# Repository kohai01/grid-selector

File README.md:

# Grid Selector(bureddo 15)
a 3x5 keypad for operators to select which grid to place the game pieces on

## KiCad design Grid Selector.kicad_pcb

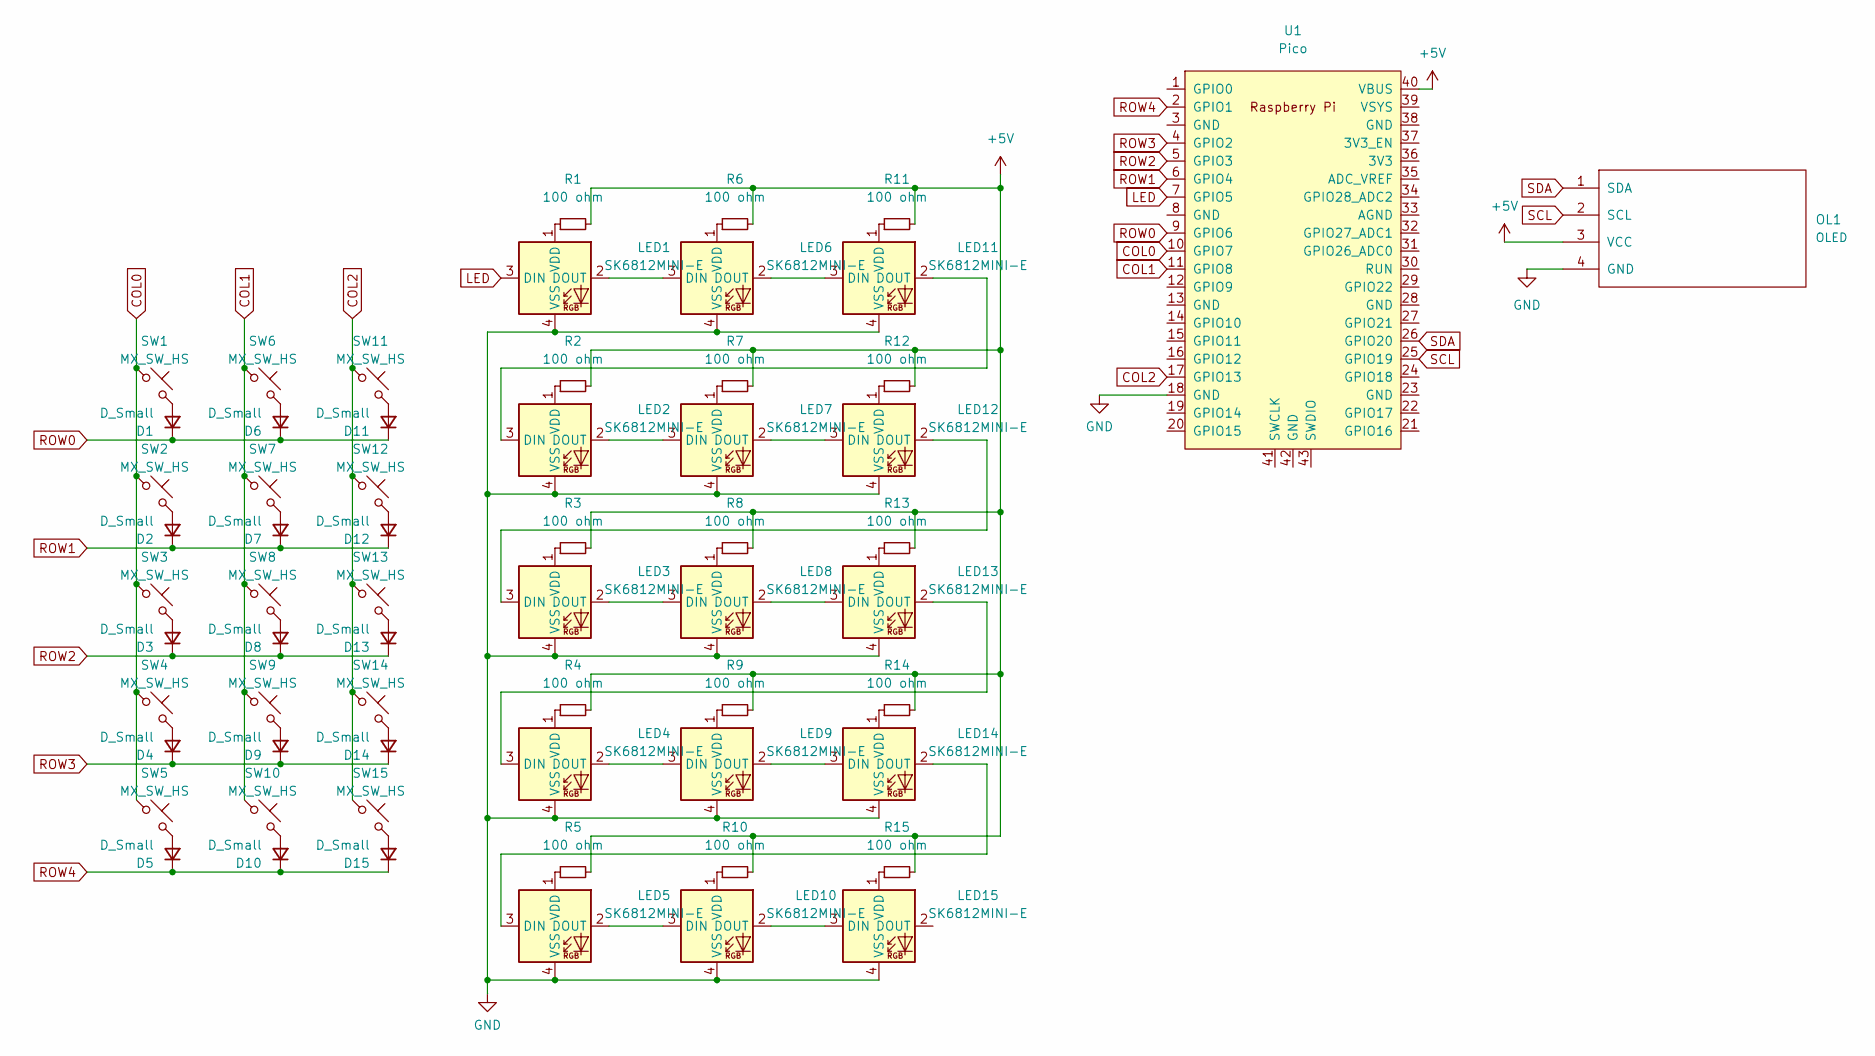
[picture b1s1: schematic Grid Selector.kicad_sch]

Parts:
D1, D2, D3, D4, D5, D6, D7, D8, D9, D10, D11, D12, D13, D14, D15: D_Small; D_SOD-123
LED1, LED2, LED3, LED4, LED5, LED6, LED7, LED8, LED9, LED10, LED11, LED12, LED13, LED14, LED15: SK6812MINI-E; LED_6028R
OL1: OLED; OLED_v2
R1, R2, R3, R4, R5, R6, R7, R8, R9, R10, R11, R12, R13, R14, R15: 100 ohm; R_0805_2012Metric
SW1, SW2, SW3, SW4, SW5, SW6, SW7, SW8, SW9, SW10, SW11, SW12, SW13, SW14, SW15: MX_SW_HS; SW_MX_HS_1u
U1: Pico; RPi_Pico_SMD_TH

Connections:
+5V: OL1.3 (VCC), R1.2, R2.2, R3.2, R4.2, R5.2, R6.2, R7.2, R8.2, R9.2, R10.2, R11.2, R12.2, R13.2, R14.2, R15.2, U1.40 (VBUS)
COL0: SW1.1, SW2.1, SW3.1, SW4.1, SW5.1, U1.10 (GPIO7)
COL1: SW6.1, SW7.1, SW8.1, SW9.1, SW10.1, U1.11 (GPIO8)
COL2: SW11.1, SW12.1, SW13.1, SW14.1, SW15.1, U1.17 (GPIO13)
GND: LED1.4 (VSS), LED2.4 (VSS), LED3.4 (VSS), LED4.4 (VSS), LED5.4 (VSS), LED6.4 (VSS), LED7.4 (VSS), LED8.4 (VSS), LED9.4 (VSS), LED10.4 (VSS), LED11.4 (VSS), LED12.4 (VSS), LED13.4 (VSS), LED14.4 (VSS), LED15.4 (VSS), OL1.4 (GND), U1.18 (GND)
LED: LED1.3 (DIN), U1.7 (GPIO5)
unnamed: D1.2 (A), SW1.2
unnamed: D2.2 (A), SW2.2
unnamed: D3.2 (A), SW3.2
unnamed: D4.2 (A), SW4.2
unnamed: D5.2 (A), SW5.2
unnamed: D6.2 (A), SW6.2
unnamed: D7.2 (A), SW7.2
unnamed: D8.2 (A), SW8.2
unnamed: D9.2 (A), SW9.2
unnamed: D10.2 (A), SW10.2
unnamed: D11.2 (A), SW11.2
unnamed: D12.2 (A), SW12.2
unnamed: D13.2 (A), SW13.2
unnamed: D14.2 (A), SW14.2
unnamed: D15.2 (A), SW15.2
unnamed: LED1.1 (VDD), R1.1
unnamed: LED1.2 (DOUT), LED6.3 (DIN)
unnamed: LED5.2 (DOUT), LED10.3 (DIN)
unnamed: LED2.2 (DOUT), LED7.3 (DIN)
unnamed: LED8.1 (VDD), R8.1
unnamed: LED8.2 (DOUT), LED13.3 (DIN)
unnamed: LED3.2 (DOUT), LED8.3 (DIN)
unnamed: LED9.2 (DOUT), LED14.3 (DIN)
unnamed: LED4.2 (DOUT), LED9.3 (DIN)
unnamed: LED2.3 (DIN), LED11.2 (DOUT)
unnamed: LED6.2 (DOUT), LED11.3 (DIN)
unnamed: LED3.3 (DIN), LED12.2 (DOUT)
unnamed: LED7.2 (DOUT), LED12.3 (DIN)
unnamed: LED4.3 (DIN), LED13.2 (DOUT)
unnamed: LED5.3 (DIN), LED14.2 (DOUT)
unnamed: LED15.1 (VDD), R15.1
unnamed: LED10.2 (DOUT), LED15.3 (DIN)
unnamed: LED2.1 (VDD), R2.1
unnamed: LED3.1 (VDD), R3.1
unnamed: LED4.1 (VDD), R4.1
unnamed: LED5.1 (VDD), R5.1
unnamed: LED6.1 (VDD), R6.1
unnamed: LED7.1 (VDD), R7.1
unnamed: LED9.1 (VDD), R9.1
unnamed: LED10.1 (VDD), R10.1
unnamed: LED11.1 (VDD), R11.1
unnamed: LED12.1 (VDD), R12.1
unnamed: LED13.1 (VDD), R13.1
unnamed: LED14.1 (VDD), R14.1
ROW0: D1.1 (K), D6.1 (K), D11.1 (K), U1.9 (GPIO6)
ROW1: D2.1 (K), D7.1 (K), D12.1 (K), U1.6 (GPIO4)
ROW2: D3.1 (K), D8.1 (K), D13.1 (K), U1.5 (GPIO3)
ROW3: D4.1 (K), D9.1 (K), D14.1 (K), U1.4 (GPIO2)
ROW4: D5.1 (K), D10.1 (K), D15.1 (K), U1.2 (GPIO1)
SCL: OL1.2 (SCL), U1.25 (GPIO19)
SDA: OL1.1 (SDA), U1.26 (GPIO20)

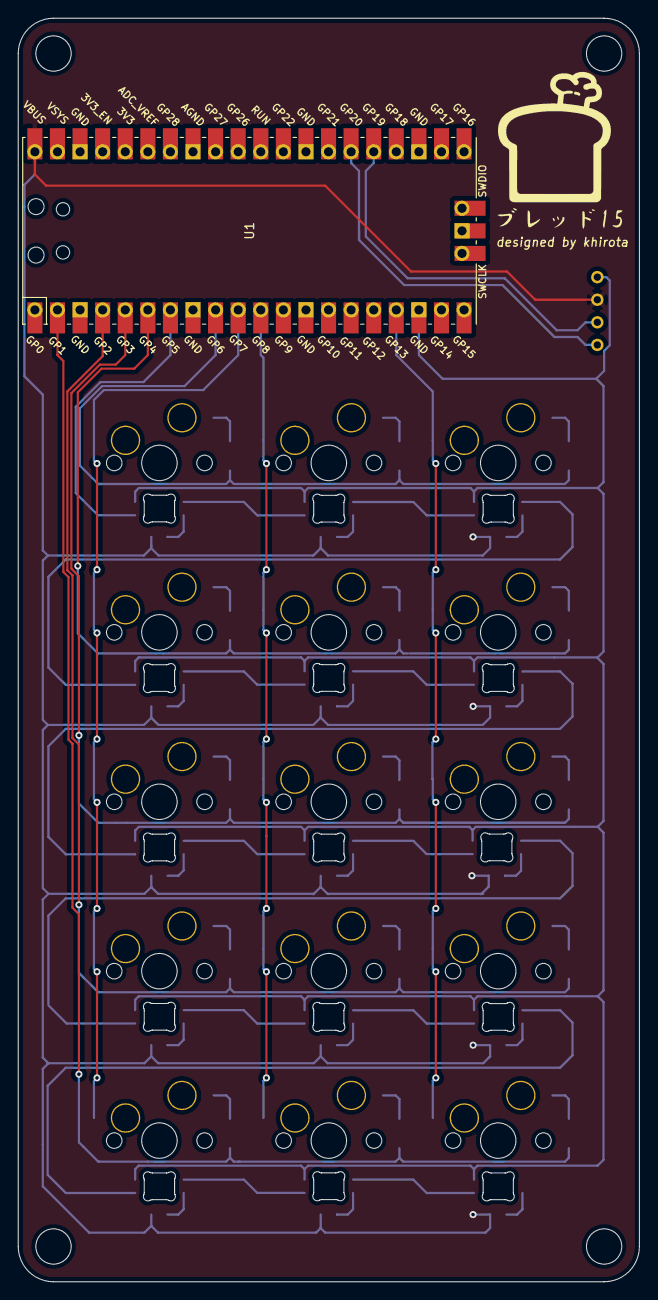
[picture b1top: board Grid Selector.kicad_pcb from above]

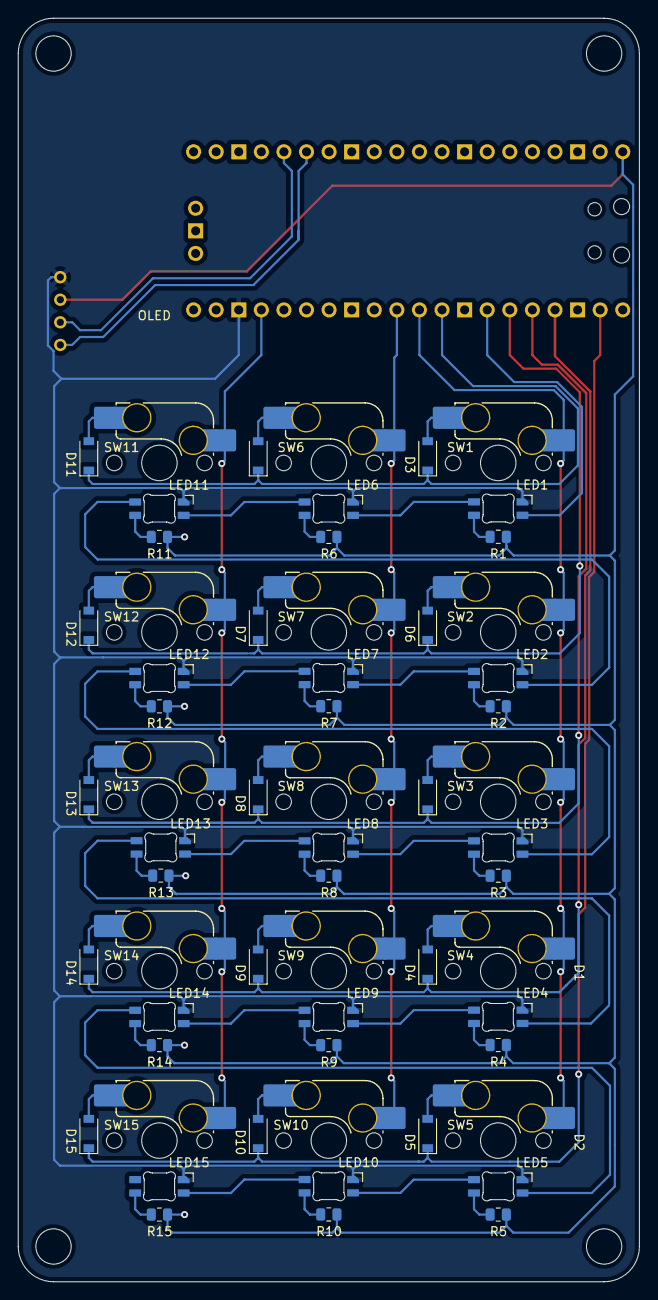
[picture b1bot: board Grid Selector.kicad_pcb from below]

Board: 2 copper layers, 69.9 x 142.1 mm, 62 parts (60 on the bottom side), 57 nets.

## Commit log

2023-02-03 added submodule
2023-02-03 initial setup
2023-02-03 made key matrix
2023-02-03 added raspi pico library
2023-02-04 added oled library and finished schematics
2023-02-04 placed switch matrix
2023-02-04 updated switch matrix
2023-02-04 added current limiting resistors to led chain
2023-02-05 routed switch matrix and led chain
2023-02-05 connected switch matrix and led chain to pico
2023-02-05 routed oled
2023-02-05 cleaned up pcb
2023-02-05 added holes for mounting
2023-02-05 added logos
2023-02-07 created gerber file
2023-03-05 reduced the size to 15 keys
2023-03-07 generated gerber file
2023-03-07 added image
2023-05-17 added 3d printed case files
